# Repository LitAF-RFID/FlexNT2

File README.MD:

# LitAF FlexNT2
This device is a miniaturised NFC tag that also powers a RGB auto cycling LED.

## Demos:
- Fast Falsh vs Slow Falsh - https://www.youtube.com/shorts/PIb9lqYM2UI
- Range Test - https://www.youtube.com/watch?v=-AcRS_bvTmE

## Schematic

## Note
This was designed based on an idea provided by somone else and I made it for them and released it like this so that they and anyone else can use it. The design was reviewied and slightly modified by this person, those changes have been included.

## Manufacturing Info
This design was created with the PCBWay 2 layer flex PCB manufacturing specifications in mind. If you order this using the CAM files provided, you need to order with 1oz copper.

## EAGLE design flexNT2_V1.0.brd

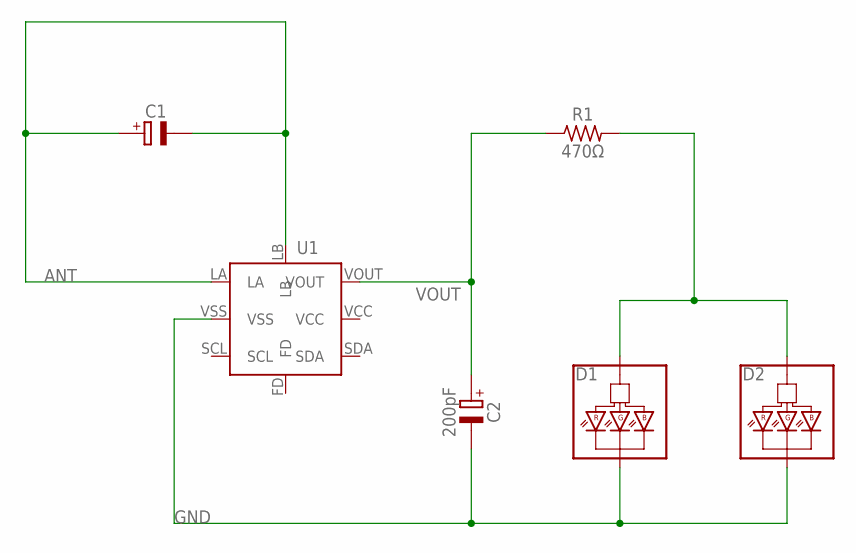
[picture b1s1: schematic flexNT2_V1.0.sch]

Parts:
C1: C_POL_0603_FLEX; 0603_FLEX_C_POL
C2: 200pF; 0603_FLEX_C_POL
D1, D2: CZINELIGHT_0807RGBFF; 0807RGBFF_CZINELIGHT
R1: 470Ω; 0603_FLEX
U1: NTAG-I2C+; XQFN8_NTAG-I2C+

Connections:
ANODE: D1.P$1 (A), D2.P$1 (A), R1.P$2 (2)
ANT: C1.P$1 (+), C1.P$2 (-), U1.LA, U1.LB
GND: C2.P$2 (-), D1.P$2 (C), D2.P$2 (C), U1.VSS
VOUT: C2.P$1 (+), R1.P$1 (1), U1.VOUT

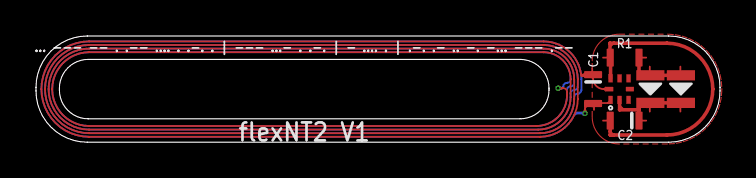
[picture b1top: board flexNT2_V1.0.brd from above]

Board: 2 copper layers, 38.0 x 5.9 mm, 6 parts (0 on the bottom side), 4 nets.

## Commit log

2024-04-04 Initial Design
2024-04-04 Crop PCB renders
